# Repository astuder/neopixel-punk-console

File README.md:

# NeoPixel Punk Console

The goal of this project is to display colorful patterns on a strip of WS2812 or SK6812 RGB LEDs (aka NeoPixels) without the help of an MCU.

This repository contains the design files for the hardware.
* [punk-console-main](neopixel-punk-main): RGB LED driver circuit
* [punk-console-oscillator](neopixel-punk-oscillator): Pattern generator circuit

Both folders contain a PDF of the schematic and the EDA project created with [KiCad](https://www.kicad.org/) version 6.0.

A detailed discussion of the design is published [here](https://hackaday.io/project/183093-neopixel-punk-console).

Featured on [Hackaday](https://hackaday.com/2022/01/01/neopixel-punk-console-drives-ws2812s-using-555-timers/)

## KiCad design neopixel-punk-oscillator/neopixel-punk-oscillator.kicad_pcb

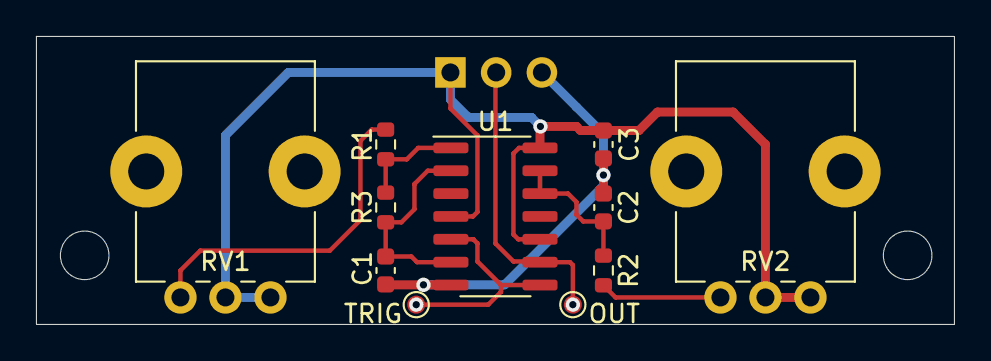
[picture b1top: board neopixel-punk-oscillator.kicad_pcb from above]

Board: 2 copper layers, 51.0 x 16.0 mm, 14 parts (1 on the bottom side), 9 nets.

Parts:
C1, C2: 0.01uF; C_0603_1608Metric
C3: 0.1uF; C_0603_1608Metric
H1, H2: MountingHole; MountingHole_2.7mm_M2.5
J1: Conn_01x03; PinHeader_1x03_P2.54mm_Vertical
R1: 1K; R_0603_1608Metric
R2, R3: 100R; R_0603_1608Metric
RV1: 1M; Potentiometer_Bourns_PTV09A-1_Single_Vertical
RV2: 10K; Potentiometer_Bourns_PTV09A-1_Single_Vertical
TP1, TP2: TestPoint; TestPoint_Pad_D1.0mm
U1: TLC556; SOIC-14_3.9x8.7mm_P1.27mm

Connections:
+5V: C3.1, J1.1, RV1.1, RV1.2, RV2.1, RV2.2, U1.4, U1.10, U1.14
/OUT: J1.2, TP2.1, U1.9
/TRIG: TP1.1, U1.5, U1.8
GND: C1.2, C2.2, C3.2, J1.3, U1.7
unnamed: C1.1, R3.2, U1.2, U1.6
unnamed: C2.1, R2.2, U1.12, U1.13
unnamed: R1.1, RV1.3
unnamed: R1.2, R3.1, U1.1
unnamed: R2.1, RV2.3

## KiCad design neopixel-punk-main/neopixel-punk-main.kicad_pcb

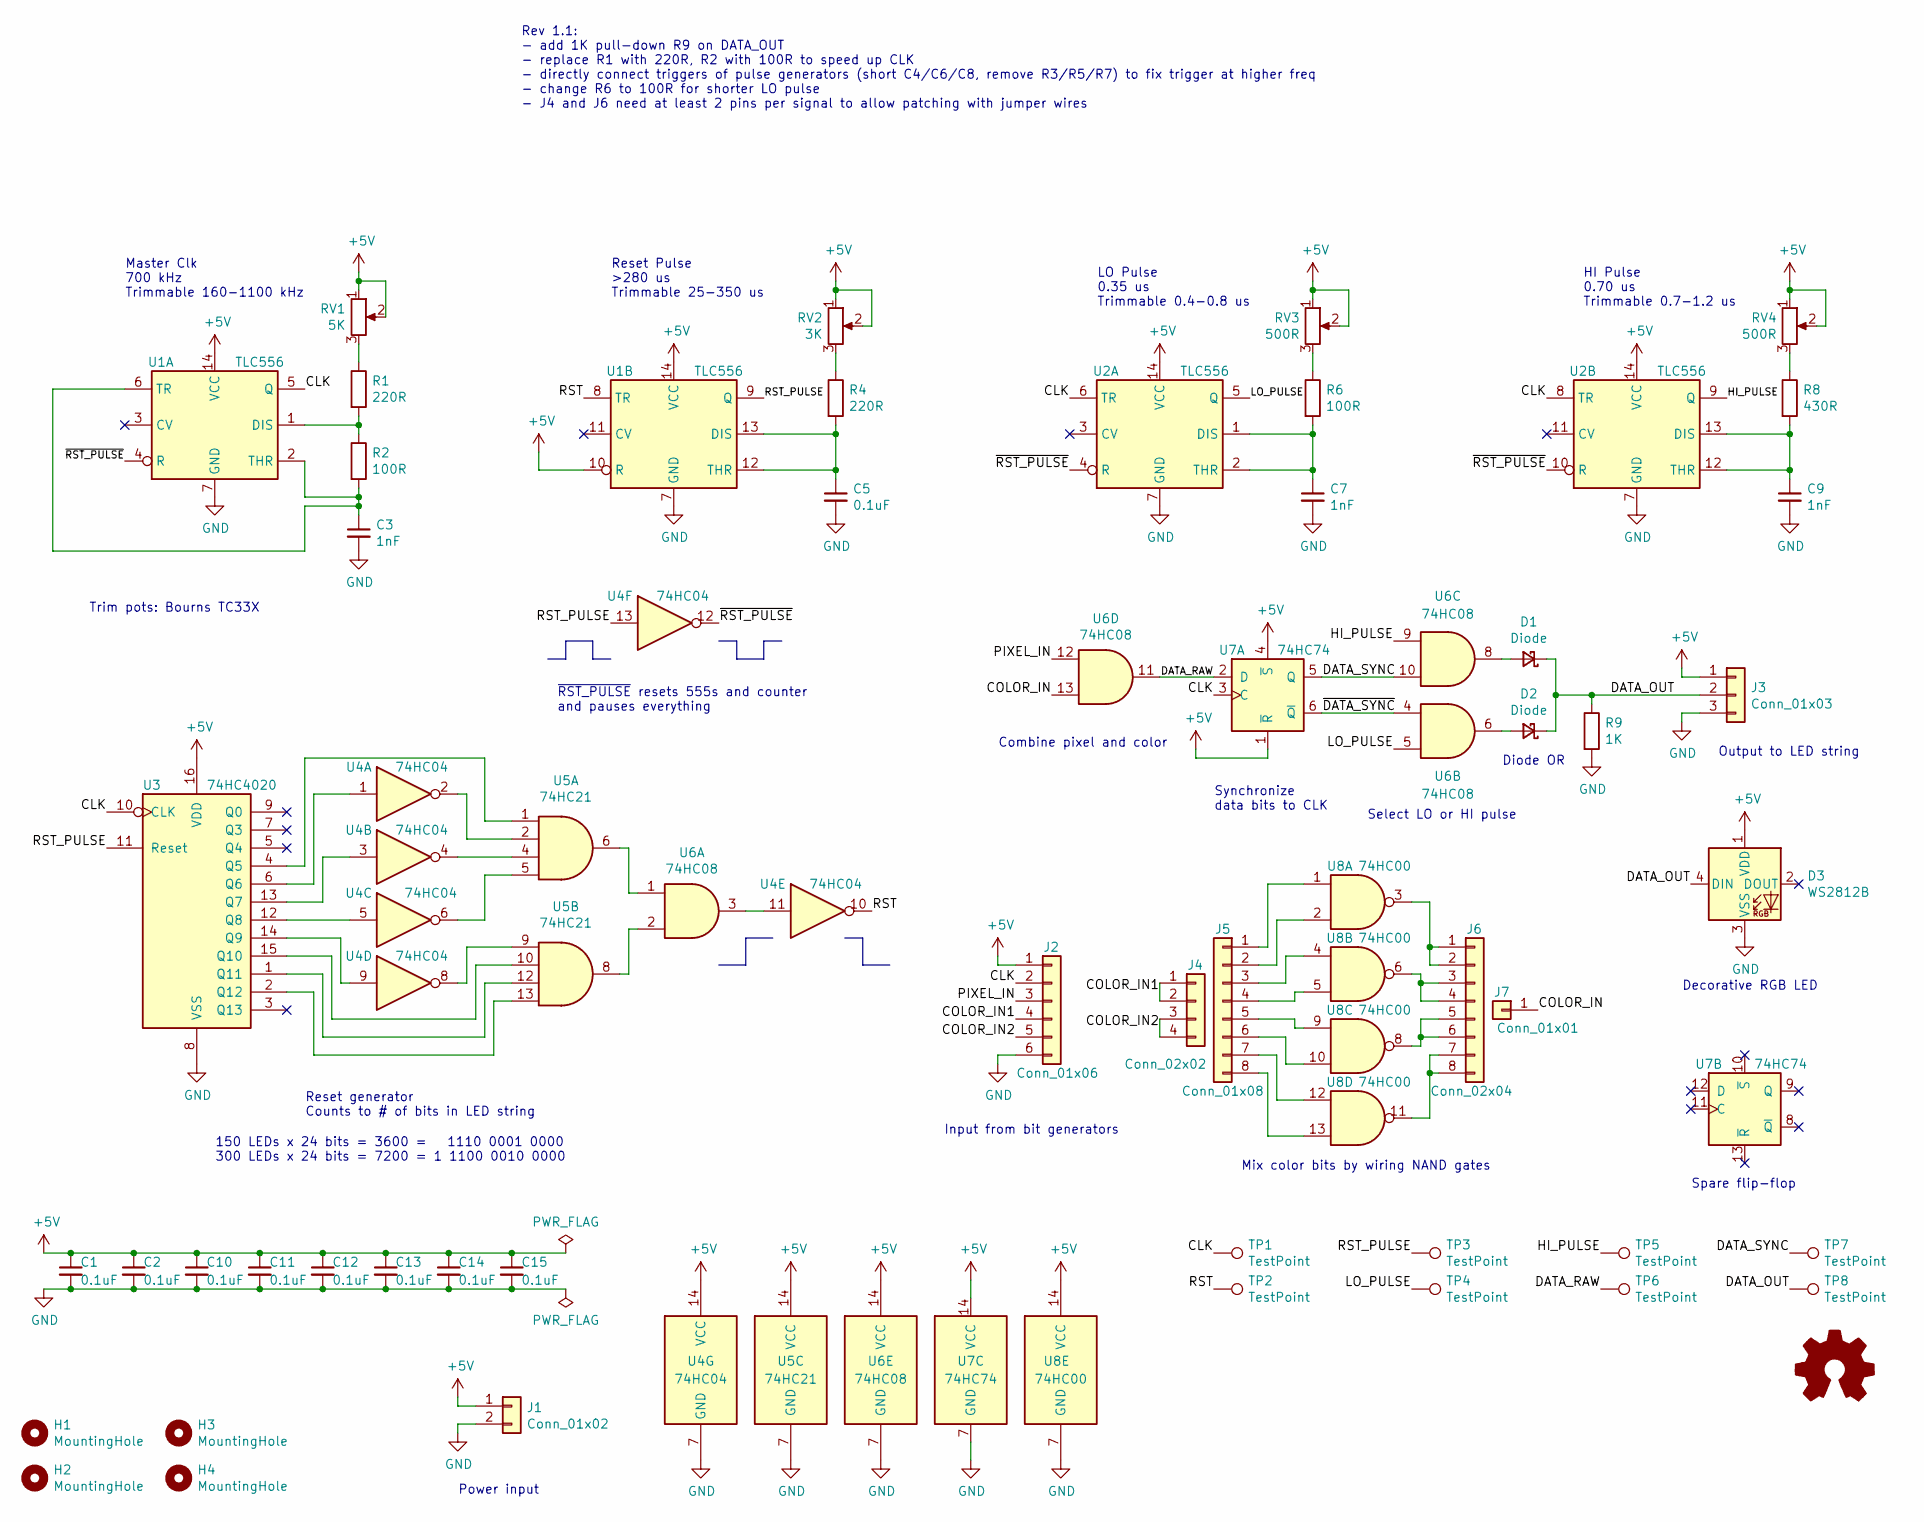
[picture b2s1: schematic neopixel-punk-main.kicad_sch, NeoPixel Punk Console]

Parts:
C1, C2, C5, C10, C11, C12, C13, C14, C15: 0.1uF; C_0603_1608Metric
C3, C7, C9: 1nF; C_0603_1608Metric
D1, D2: Diode; D_SOD-523
D3: WS2812B; LED_WS2812B_PLCC4_5.0x5.0mm_P3.2mm
H1, H2, H3, H4: MountingHole; MountingHole_2.7mm_M2.5
J1: Conn_01x02; PinHeader_1x02_P2.54mm_Vertical
J2: Conn_01x06; PinHeader_2x02_P2.54mm_Vertical
J3: Conn_01x03; PinHeader_1x03_P2.54mm_Vertical
J4: Conn_02x02; PinHeader_1x02_P2.54mm_Vertical
J5: Conn_01x08; PinHeader_1x08_P2.54mm_Vertical
J6: Conn_02x04; PinHeader_2x04_P2.54mm_Vertical
J7: Conn_01x01; PinHeader_1x01_P2.54mm_Vertical
R1, R4: 220R; R_0603_1608Metric
R2, R6: 100R; R_0603_1608Metric
R8: 430R; R_0603_1608Metric
R9: 1K; R_0603_1608Metric
RV1: 5K; Potentiometer_Bourns_TC33X_Vertical
RV2: 3K; Potentiometer_Bourns_TC33X_Vertical
RV3, RV4: 500R; Potentiometer_Bourns_TC33X_Vertical
TP1, TP2, TP3, TP4, TP5, TP6, TP7, TP8: TestPoint; TestPoint_Pad_D1.0mm
U1, U2: TLC556; SOIC-14_3.9x8.7mm_P1.27mm
U3: 74HC4020; SOIC-16_3.9x9.9mm_P1.27mm
U4: 74HC04; SOIC-14_3.9x8.7mm_P1.27mm
U5: 74HC21; SOIC-14_3.9x8.7mm_P1.27mm
U6: 74HC08; SOIC-14_3.9x8.7mm_P1.27mm
U7: 74HC74; SOIC-14_3.9x8.7mm_P1.27mm
U8: 74HC00; SOIC-14_3.9x8.7mm_P1.27mm

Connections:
+5V: C1.1, C2.1, C10.1, C11.1, C12.1, C13.1, C14.1, C15.1, D3.1 (VDD), J1.1, J2.1, J3.1, RV1.1, RV1.2, RV2.1, RV2.2, RV3.1, RV3.2, RV4.1, RV4.2, U1.10 (R), U1.14 (VCC), U2.14 (VCC), U3.16 (VDD), U4.14 (VCC), U5.14 (VCC), U6.14 (VCC), U7.1 (~R), U7.4 (~S), U7.14 (VCC), U8.14 (VCC)
/CLK: J2.2, TP1.1, U1.5 (Q), U2.6 (TR), U2.8 (TR), U3.10 (CLK), U7.3 (C)
/COLOR_IN: J7.1, U6.13
/COLOR_IN1: J2.4, J4.1, J4.2
/COLOR_IN2: J2.5, J4.3, J4.4
/DATA_OUT: D1.1 (K), D2.1 (K), D3.4 (DIN), J3.2, R9.1, TP8.1
/DATA_RAW: TP6.1, U6.11, U7.2 (D)
/DATA_SYNC: TP7.1, U6.10, U7.5 (Q)
/HI_PULSE: TP5.1, U2.9 (Q), U6.9
/LO_PULSE: TP4.1, U2.5 (Q), U6.5
/PIXEL_IN: J2.3, U6.12
/RST: TP2.1, U1.8 (TR), U4.10
/RST_PULSE: TP3.1, U1.9 (Q), U3.11 (Reset), U4.13
/~DATA_SYNC: U6.4, U7.6 (~Q)
/~RST_PULSE: U1.4 (R), U2.4 (R), U2.10 (R), U4.12
GND: C1.2, C2.2, C3.2, C5.2, C7.2, C9.2, C10.2, C11.2, C12.2, C13.2, C14.2, C15.2, D3.3 (VSS), J1.2, J2.6, J3.3, R9.2, U1.7 (GND), U2.7 (GND), U3.8 (VSS), U4.7 (GND), U5.7 (GND), U6.7 (GND), U7.7 (GND), U8.7 (GND)
unnamed: C3.1, R2.2, U1.2 (THR), U1.6 (TR)
unnamed: C5.1, R4.2, U1.12 (THR), U1.13 (DIS)
unnamed: C7.1, R6.2, U2.1 (DIS), U2.2 (THR)
unnamed: C9.1, R8.2, U2.12 (THR), U2.13 (DIS)
unnamed: D1.2 (A), U6.8
unnamed: D2.2 (A), U6.6
unnamed: J5.1, U8.1
unnamed: J5.2, U8.2
unnamed: J5.3, U8.4
unnamed: J5.4, U8.5
unnamed: J5.5, U8.9
unnamed: J5.6, U8.10
unnamed: J5.7, U8.12
unnamed: J5.8, U8.13
unnamed: J6.1, J6.2, U8.3
unnamed: J6.3, J6.4, U8.6
unnamed: J6.5, J6.6, U8.8
unnamed: J6.7, J6.8, U8.11
unnamed: R1.1, RV1.3
unnamed: R1.2, R2.1, U1.1 (DIS)
unnamed: R4.1, RV2.3
unnamed: R6.1, RV3.3
unnamed: R8.1, RV4.3
unnamed: U3.1 (Q11), U5.12
unnamed: U3.2 (Q12), U5.13
unnamed: U3.4 (Q5), U5.1
unnamed: U3.6 (Q6), U4.1
unnamed: U3.12 (Q8), U4.5
unnamed: U3.13 (Q7), U4.3
unnamed: U3.14 (Q9), U4.9
unnamed: U3.15 (Q10), U5.10
unnamed: U4.2, U5.2
unnamed: U4.4, U5.4
unnamed: U4.6, U5.5
unnamed: U4.8, U5.9
unnamed: U4.11, U6.3
unnamed: U5.6, U6.1
unnamed: U5.8, U6.2

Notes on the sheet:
Reset generator Counts to # of bits in LED string
Synchronize data bits to CLK
Master Clk 700 kHz Trimmable 160-1100 kHz
Output to LED string
Decorative RGB LED
Select LO or HI pulse
HI Pulse 0.70 us Trimmable 0.7-1.2 us
Reset Pulse >280 us Trimmable 25-350 us
Combine pixel and color
Power input
Trim pots: Bourns TC33X
Mix color bits by wiring NAND gates
Input from bit generators
~{RST_PULSE} resets 555s and counter and pauses everything
Spare flip-flop
150 LEDs x 24 bits = 3600 = 1110 0001 0000 300 LEDs x 24 bits = 7200 = 1 1100 0010 0000
Rev 1.1: - add 1K pull-down R9 on DATA_OUT - replace R1 with 220R, R2 with 100R to speed up CLK - directly connect triggers of pulse generators (short C4/C6/C8, remove R3/R5/R7) to fix trigger at higher freq - change R6 to 100R for shorter LO pulse - J4 and J6 need at least 2 pins per signal to all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
LO Pulse 0.35 us Trimmable 0.4-0.8 us
Diode OR

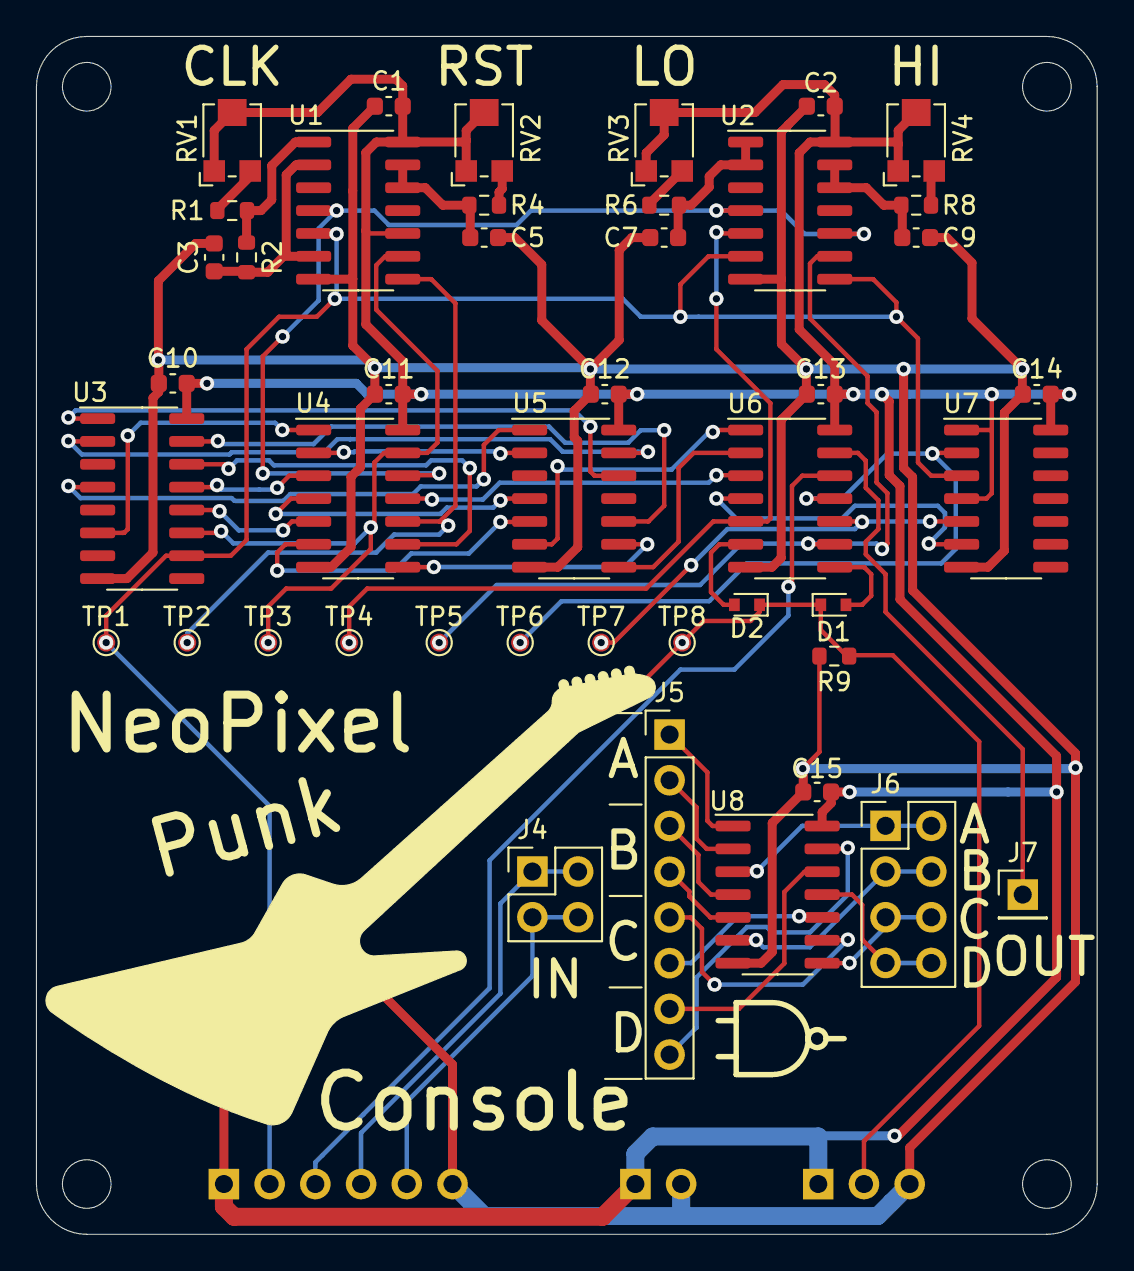
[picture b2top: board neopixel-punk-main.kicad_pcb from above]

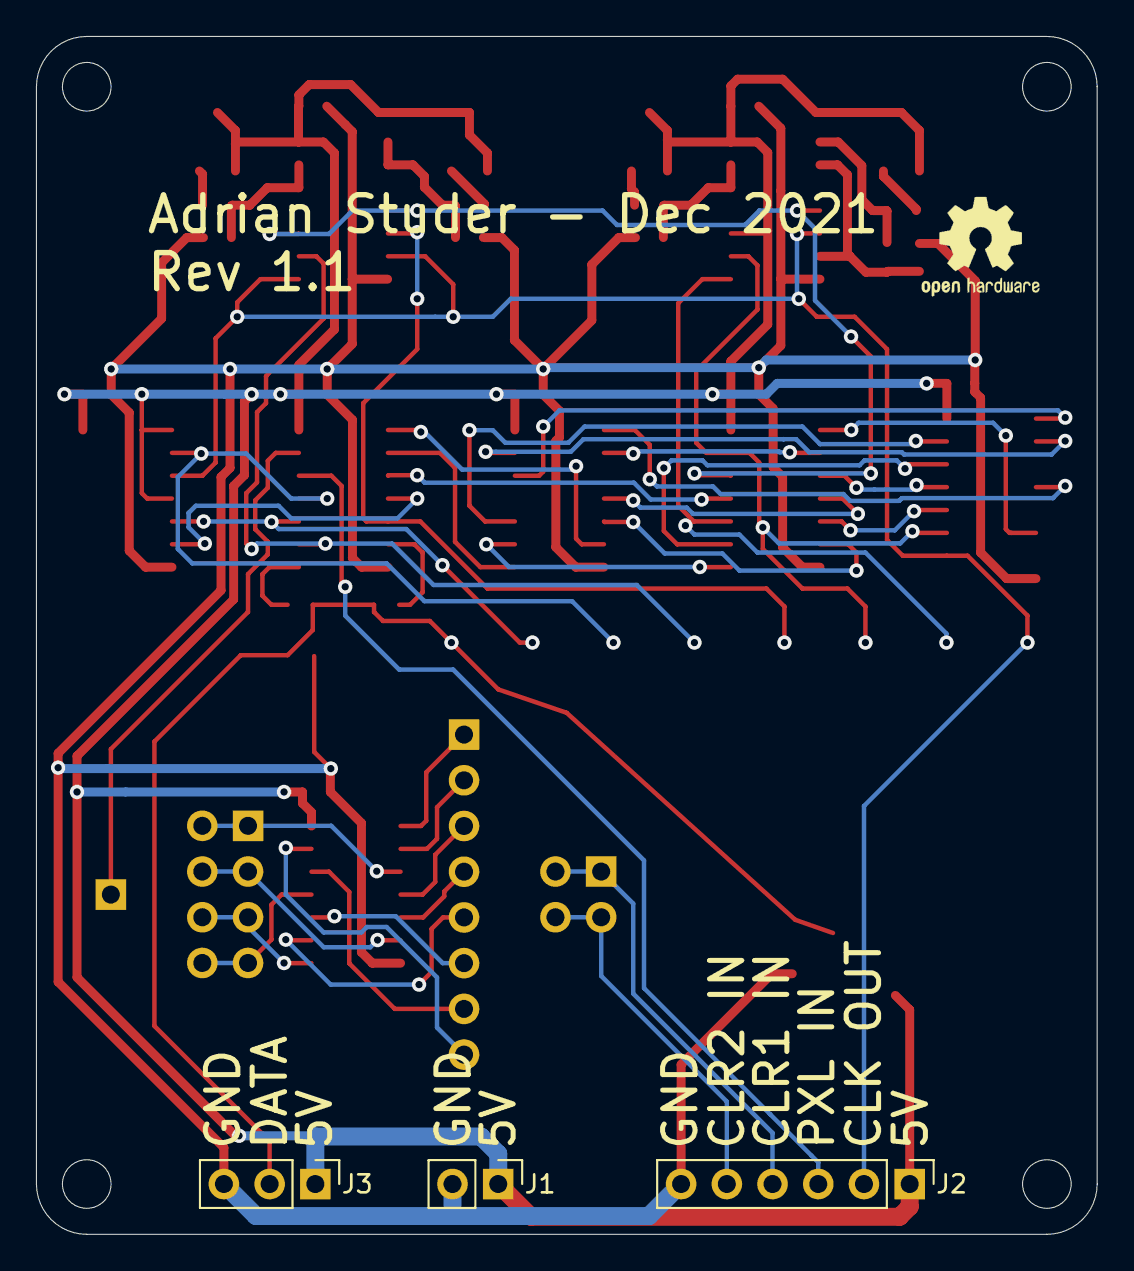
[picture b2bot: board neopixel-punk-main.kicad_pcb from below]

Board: 2 copper layers, 58.9 x 66.5 mm, 52 parts (3 on the bottom side), 54 nets.

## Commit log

2021-12-29 hw version 1.1
2021-12-29 add README
2021-12-29 Create LICENSE
2021-12-29 fix links
2021-12-31 black PCB color
2021-12-31 replaced image
2022-01-09 add HaD link
